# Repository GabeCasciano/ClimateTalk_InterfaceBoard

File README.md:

# ClimateTalk_InterfaceBoard
Climate Talk Interface Board

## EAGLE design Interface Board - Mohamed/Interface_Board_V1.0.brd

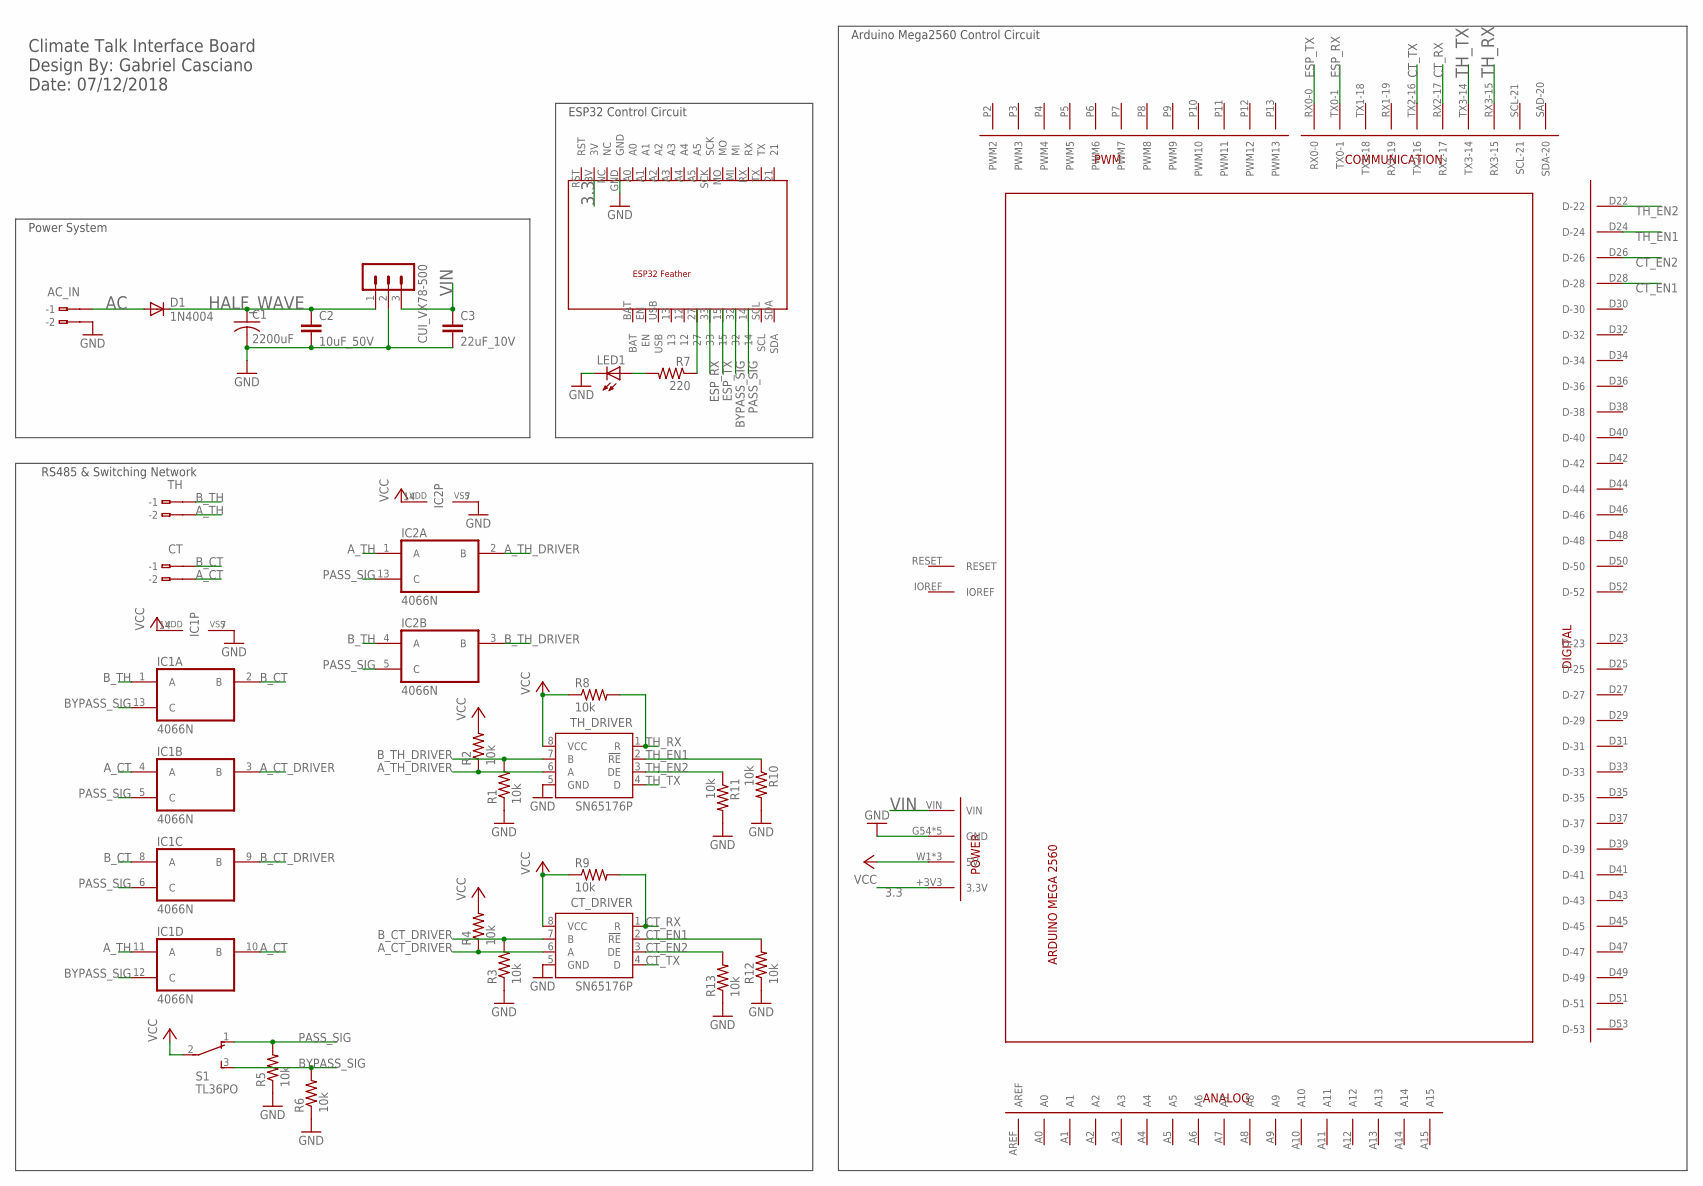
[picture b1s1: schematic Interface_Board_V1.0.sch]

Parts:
AC_IN: 233-102
C1: 2200uF; C102-054X133
C2: 10uF_50V; C025-025X050
C3: 22uF_10V; C025-025X050
CT: 233-102
CT_DRIVER: SN65176P; DIL08
CUI_VX78-500: MA03-1
D1: 1N4004; DO41-10
IC1, IC2: 4066N; DIL14
LED1: LED5MM
R1, R2, R3, R4, R5, R6, R8, R9, R10, R11, R12, R13: 10k; 0204/7
R7: 220; 0204/7
S1: TL36PO; TL3XPO
S2: ESP32
TH: 233-102
TH_DRIVER: SN65176P; DIL08
U$1: BOARD_ARDUINO-MEGA; BOARD_ARDUINO_MEGA

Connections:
3.3: S2.3V, U$1.+3V3 (3.3V)
AC: AC_IN.B1 (B-1), D1.A
A_CT: CT.B2 (B-2), IC1.4 (A), IC1.10 (B)
A_CT_DRIVER: CT_DRIVER.6 (A), IC1.3 (B), R4.1
A_TH: IC1.11 (A), IC2.1 (A), TH.B2 (B-2)
A_TH_DRIVER: IC2.2 (B), R2.1, TH_DRIVER.6 (A)
BYPASS_SIG: IC1.12 (C), IC1.13 (C), R6.2, S1.3 (S), S2.32
B_CT: CT.B1 (B-1), IC1.2 (B), IC1.8 (A)
B_CT_DRIVER: CT_DRIVER.7 (B), IC1.9 (B), R3.2
B_TH: IC1.1 (A), IC2.4 (A), TH.B1 (B-1)
B_TH_DRIVER: IC2.3 (B), R1.2, TH_DRIVER.7 (B)
CT_EN1: CT_DRIVER.2 (!RE), R12.2, U$1.D28 (D-28)
CT_EN2: CT_DRIVER.3 (DE), R13.2, U$1.D26 (D-26)
CT_RX: CT_DRIVER.1 (R), R9.2, U$1.RX2-17
CT_TX: CT_DRIVER.4 (D), U$1.TX2-16
ESP_RX: S2.33, U$1.TX0-1
ESP_TX: S2.15, U$1.RX0-0
GND: AC_IN.B2 (B-2), C1.2, C2.2, C3.2, CT_DRIVER.5 (GND), CUI_VX78-500.2, IC1.7 (VSS), IC2.7 (VSS), LED1.K (C), R1.1, R3.1, R5.1, R6.1, R10.2, R11.2, R12.1, R13.1, S2.GND, TH_DRIVER.5 (GND), U$1.G54 (GND), U$1.G55 (GND), U$1.G56 (GND), U$1.G57 (GND), U$1.G58 (GND)
HALF_WAVE: C1.1, C2.1, CUI_VX78-500.1, D1.C
unnamed: LED1.A, R7.2
unnamed: R7.1, S2.27
PASS_SIG: IC1.5 (C), IC1.6 (C), IC2.5 (C), IC2.13 (C), R5.2, S1.1 (O), S2.14
TH_EN1: R10.1, TH_DRIVER.2 (!RE), U$1.D24 (D-24)
TH_EN2: R11.1, TH_DRIVER.3 (DE), U$1.D22 (D-22)
TH_RX: R8.2, TH_DRIVER.1 (R), U$1.RX3-15
TH_TX: TH_DRIVER.4 (D), U$1.TX3-14
VCC: CT_DRIVER.8 (VCC), IC1.14 (VDD), IC2.14 (VDD), R2.2, R4.2, R8.1, R9.1, S1.2, TH_DRIVER.8 (VCC), U$1.W1 (5V), U$1.W2 (5V), U$1.W3 (5V)
VIN: C3.1, CUI_VX78-500.3, U$1.VIN

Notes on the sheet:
Power System
RS485 & Switching Network
ESP32 Control Circuit
Arduino Mega2560 Control Circuit
Climate Talk Interface Board Design By: Gabriel Casciano Date: 07/12/2018

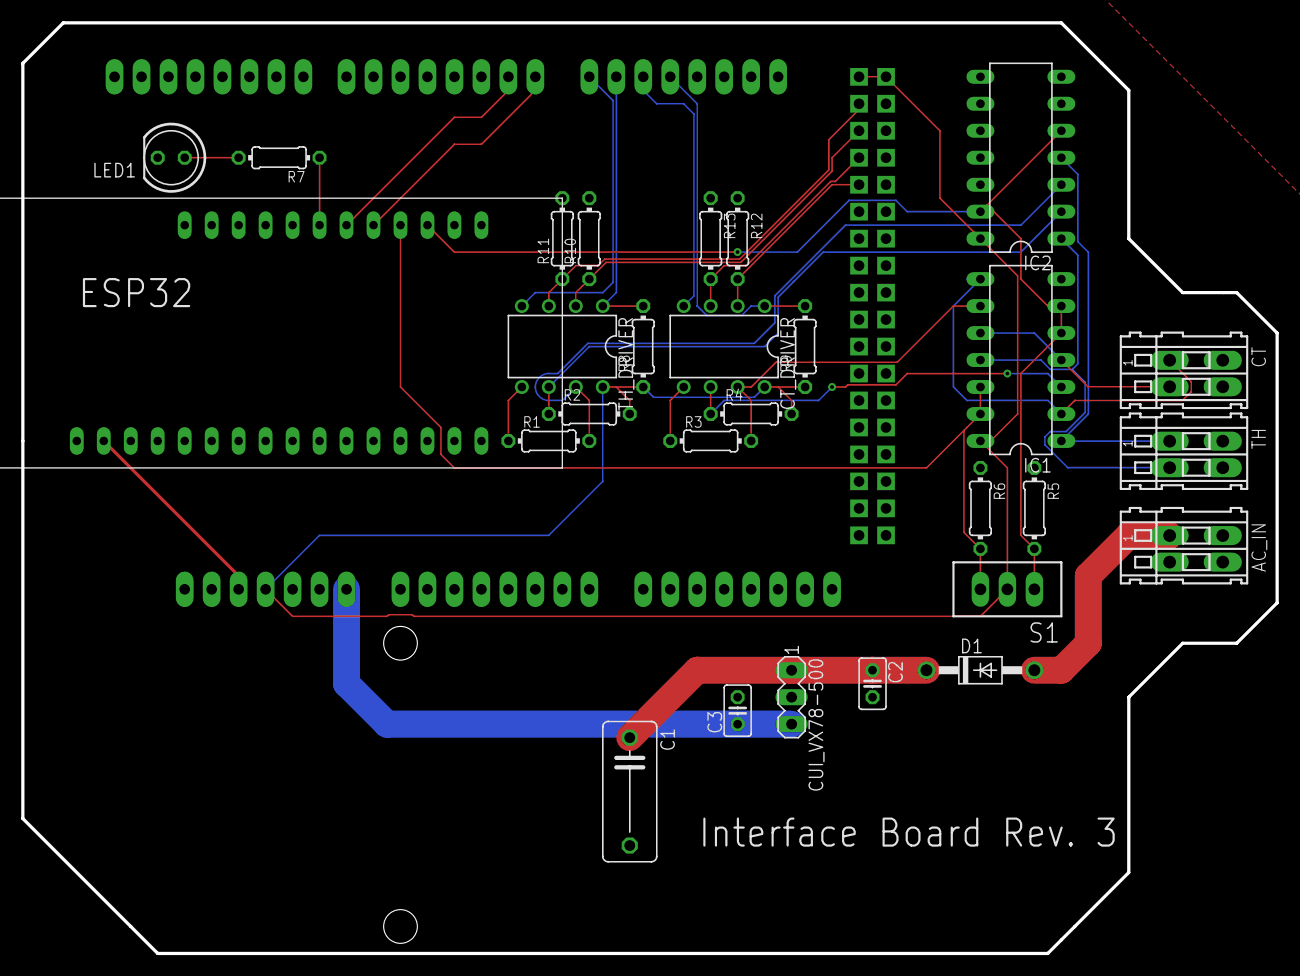
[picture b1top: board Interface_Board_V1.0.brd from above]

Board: 2 copper layers, 118.1 x 87.6 mm, 29 parts (1 on the bottom side), 28 nets.

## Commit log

2018-07-13 Interface Board Rev.3, Complete schematic and board layout.
2018-07-16 Fixed some VCC issues & added digital control signals for the kill switch
